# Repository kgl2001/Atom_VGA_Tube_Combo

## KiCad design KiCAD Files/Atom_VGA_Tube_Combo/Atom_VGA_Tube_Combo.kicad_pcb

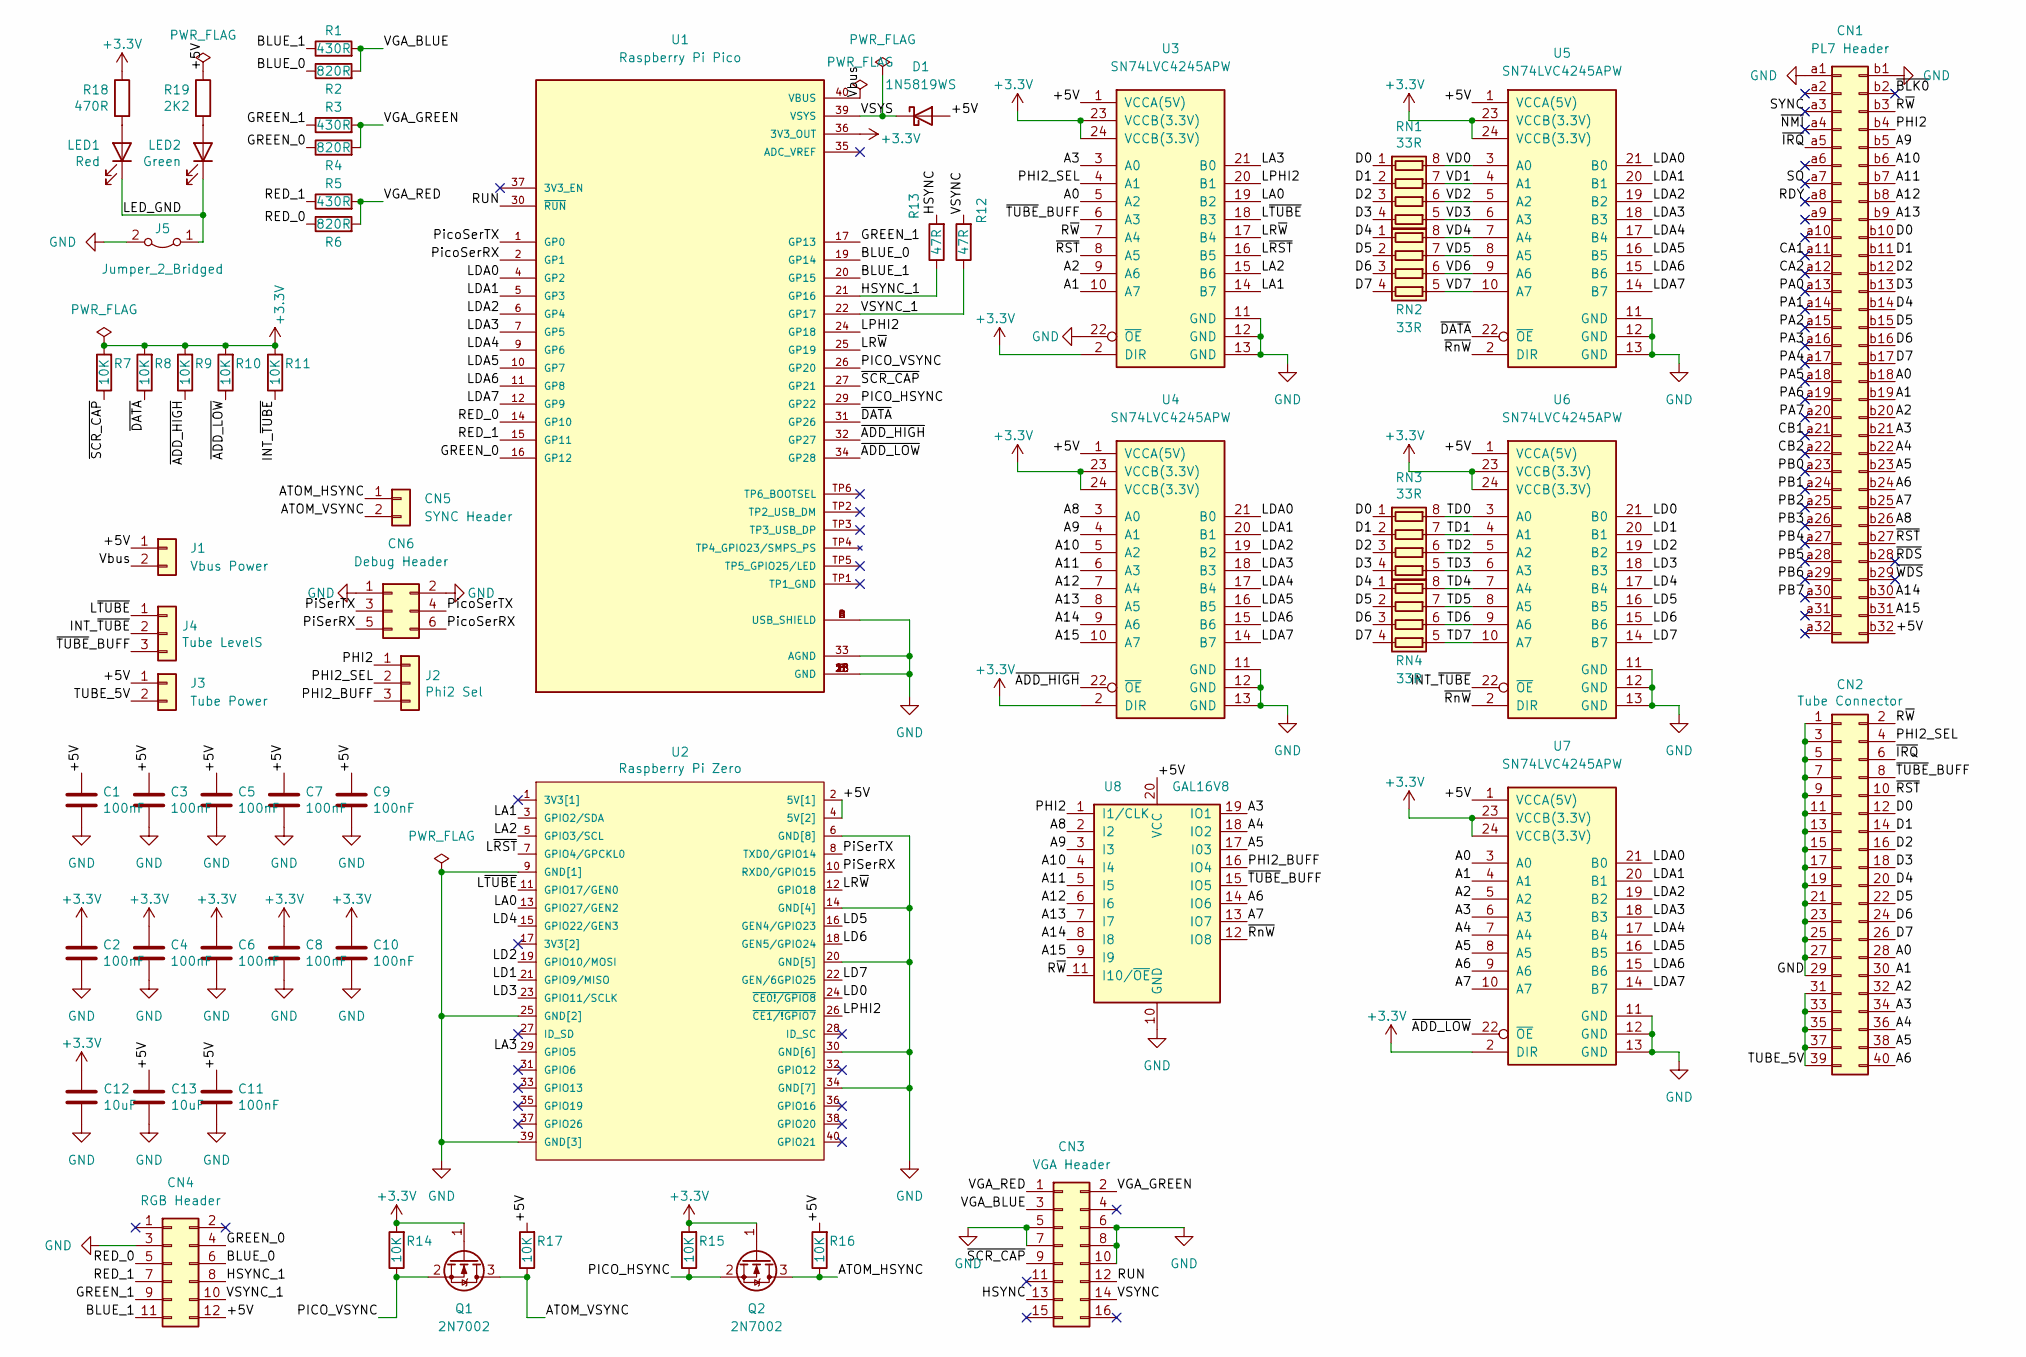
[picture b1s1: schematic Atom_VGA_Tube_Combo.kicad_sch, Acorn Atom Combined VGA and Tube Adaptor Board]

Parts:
C1, C2, C3, C4, C5, C6, C7, C8, C9, C10, C11: 100nF; C_0402_1005Metric; Tolerance 10%; JLC Part Number C1525
C12, C13: 10uF; C_0603_1608Metric; Tolerance 10%; JLC Part Number C19702
CN1: PL7 Header; DIN41612_Q_2x32_Male_Vertical_THT
CN2: Tube Connector; IDC-Header_2x20_P2.54mm_Horizontal
CN3: VGA Header; IDC-Header_2x08_P2.54mm_Vertical
CN4: RGB Header; IDC-Header_2x06_P2.54mm_Vertical
CN5: SYNC Header; PinHeader_2x01_P2.54mm_Horizontal
CN6: Debug Header; PinHeader_2x03_P2.54mm_Horizontal
D1: 1N5819WS; D_SOD-323; JLC Part Number C191023
J1: Vbus Power; PinHeader_1x02_P2.54mm_Vertical
J2: Phi2 Sel; PinHeader_1x03_P2.54mm_Vertical
J3: Tube Power; PinHeader_1x02_P2.54mm_Vertical
J4: Tube LevelS; PinHeader_1x03_P2.54mm_Vertical
J5: Jumper_2_Bridged; NetTie-2_THT_Pad1.0mmV2
LED1: Red; LED_0603_1608Metric; JLC Part Number C2286
LED2: Green; LED_0603_1608Metric; JLC Part Number C72043
Q1, Q2: 2N7002; SOT-23; JLC Part Number C8545
R1, R3, R5: 430R; R_0603_1608Metric; Tolerance 1%; JLC Part Number C23170
R2, R4, R6: 820R; R_0603_1608Metric; Tolerance 1%; JLC Part Number C23253
R7, R8, R9, R10, R11, R14, R15, R16, R17: 10K; R_0603_1608Metric; Tolerance 1%; JLC Part Number C25804
R12, R13: 47R; R_0603_1608Metric; Tolerance 1%; JLC Part Number C23182
R18: 470R; R_0603_1608Metric; Tolerance 1%; JLC Part Number C23179
R19: 2K2; R_0603_1608Metric; Tolerance 1%; JLC Part Number C4190
RN1, RN2, RN3, RN4: 33R; R_Array_Concave_4x0402; Tolerance 5%; JLC Part Number C25501
U1: Raspberry Pi Pico; RPI_PICO_DUAL_NoDebug; PARTREV 1.6
U2: Raspberry Pi Zero; RPI_ZERO_TH
U3, U4, U5, U6, U7: SN74LVC4245APW; TSSOP-24_4.4x7.8mm_P0.65mm; JLC Part Number C7859
U8: GAL16V8; DIP-20_W7.62mm

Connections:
+3.3V: C2.1, C4.1, C6.1, C8.1, C10.1, C12.1, Q1.1 (G), Q2.1 (G), R7.2, R8.2, R9.2, R10.2, R11.2, R14.2, R15.2, R18.1, U1.36 (3V3_OUT), U3.2 (DIR), U3.23 (VCCB(3.3V)), U3.24 (VCCB(3.3V)), U4.2 (DIR), U4.23 (VCCB(3.3V)), U4.24 (VCCB(3.3V)), U5.23 (VCCB(3.3V)), U5.24 (VCCB(3.3V)), U6.23 (VCCB(3.3V)), U6.24 (VCCB(3.3V)), U7.2 (DIR), U7.23 (VCCB(3.3V)), U7.24 (VCCB(3.3V))
/+5V: C1.1, C3.1, C5.1, C7.1, C9.1, C11.1, C13.1, CN1.b32, CN4.12, D1.2 (A), J1.1, J3.1, R16.2, R17.2, R19.1, U2.2 (5V[1]), U2.4 (5V[2]), U3.1 (VCCA(5V)), U4.1 (VCCA(5V)), U5.1 (VCCA(5V)), U6.1 (VCCA(5V)), U7.1 (VCCA(5V)), U8.20 (VCC)
/A0: CN1.b18, CN2.28, U3.5 (A2), U7.3 (A0)
/A1: CN1.b19, CN2.30, U3.10 (A7), U7.4 (A1)
/A2: CN1.b20, CN2.32, U3.9 (A6), U7.5 (A2)
/A3: CN1.b21, CN2.34, U3.3 (A0), U7.6 (A3), U8.19 (IO1)
/A4: CN1.b22, CN2.36, U7.7 (A4), U8.18 (IO2)
/A5: CN1.b23, CN2.38, U7.8 (A5), U8.17 (I03)
/A6: CN1.b24, CN2.40, U7.9 (A6), U8.14 (IO6)
/A7: CN1.b25, U7.10 (A7), U8.13 (IO7)
/A8: CN1.b26, U4.3 (A0), U8.2 (I2)
/A9: CN1.b5, U4.4 (A1), U8.3 (I3)
/A10: CN1.b6, U4.5 (A2), U8.4 (I4)
/A11: CN1.b7, U4.6 (A3), U8.5 (I5)
/A12: CN1.b8, U4.7 (A4), U8.6 (I6)
/A13: CN1.b9, U4.8 (A5), U8.7 (I7)
/A14: CN1.b30, U4.9 (A6), U8.8 (I8)
/A15: CN1.b31, U4.10 (A7), U8.9 (I9)
/ATOM_HSYNC: CN5.1, Q2.3 (D), R16.1
/ATOM_VSYNC: CN5.2, Q1.3 (D), R17.1
/BLUE_0: CN4.6, R2.1, U1.19 (GP14)
/BLUE_1: CN4.11, R1.1, U1.20 (GP15)
/CA1: CN1.a11
/CA2: CN1.a12
/CB1: CN1.a21
/CB2: CN1.a22
/D0: CN1.b10, CN2.12, RN1.1 (R1.1), RN3.1 (R1.1)
/D1: CN1.b11, CN2.14, RN1.2 (R2.1), RN3.2 (R2.1)
/D2: CN1.b12, CN2.16, RN1.3 (R3.1), RN3.3 (R3.1)
/D3: CN1.b13, CN2.18, RN1.4 (R4.1), RN3.4 (R4.1)
/D4: CN1.b14, CN2.20, RN2.1 (R1.1), RN4.1 (R1.1)
/D5: CN1.b15, CN2.22, RN2.2 (R2.1), RN4.2 (R2.1)
/D6: CN1.b16, CN2.24, RN2.3 (R3.1), RN4.3 (R3.1)
/D7: CN1.b17, CN2.26, RN2.4 (R4.1), RN4.4 (R4.1)
/GREEN_0: CN4.4, R4.1, U1.16 (GP12)
/GREEN_1: CN4.9, R3.1, U1.17 (GP13)
/HSYNC: CN3.13, R13.2
/HSYNC_1: CN4.8, R13.1, U1.21 (GP16)
/INT_~TUBE: J4.2, R11.1, U6.22 (~OE)
/LA0: U2.13 (GPIO27/GEN2), U3.19 (B2)
/LA1: U2.3 (GPIO2/SDA), U3.14 (B7)
/LA2: U2.5 (GPIO3/SCL), U3.15 (B6)
/LA3: U2.29 (GPIO5), U3.21 (B0)
/LD0: U2.24 (~CE0!/GPIO8), U6.21 (B0)
/LD1: U2.21 (GPIO9/MISO), U6.20 (B1)
/LD2: U2.19 (GPIO10/MOSI), U6.19 (B2)
/LD3: U2.23 (GPIO11/SCLK), U6.18 (B3)
/LD4: U2.15 (GPIO22/GEN3), U6.17 (B4)
/LD5: U2.16 (GEN4/GPIO23), U6.16 (B5)
/LD6: U2.18 (GEN5/GPIO24), U6.15 (B6)
/LD7: U2.22 (GEN/6GPIO25), U6.14 (B7)
/LDA0: U1.4 (GP2), U4.21 (B0), U5.21 (B0), U7.21 (B0)
/LDA1: U1.5 (GP3), U4.20 (B1), U5.20 (B1), U7.20 (B1)
/LDA2: U1.6 (GP4), U4.19 (B2), U5.19 (B2), U7.19 (B2)
/LDA3: U1.7 (GP5), U4.18 (B3), U5.18 (B3), U7.18 (B3)
/LDA4: U1.9 (GP6), U4.17 (B4), U5.17 (B4), U7.17 (B4)
/LDA5: U1.10 (GP7), U4.16 (B5), U5.16 (B5), U7.16 (B5)
/LDA6: U1.11 (GP8), U4.15 (B6), U5.15 (B6), U7.15 (B6)
/LDA7: U1.12 (GP9), U4.14 (B7), U5.14 (B7), U7.14 (B7)
/LED_GND: J5.1 (A), LED1.1 (K), LED2.1 (K)
/LPHI2: U1.24 (GP18), U2.26 (~CE1/!GPIO7), U3.20 (B1)
/LR~W: U1.25 (GP19), U2.12 (GPIO18), U3.17 (B4)
/L~RST: U2.7 (GPIO4/GPCKL0), U3.16 (B5)
/L~TUBE: J4.1, U2.11 (GPIO17/GEN0), U3.18 (B3)
/PA0: CN1.a13
/PA1: CN1.a14
/PA2: CN1.a15
/PA3: CN1.a16
/PA4: CN1.a17
/PA5: CN1.a18
/PA6: CN1.a19
/PA7: CN1.a20
/PB0: CN1.a23
/PB1: CN1.a24
/PB2: CN1.a25
/PB3: CN1.a26
/PB4: CN1.a27
/PB5: CN1.a28
/PB6: CN1.a29
/PB7: CN1.a30
/PHI2: CN1.b4, J2.1, U8.1 (I1/CLK)
/PHI2_BUFF: J2.3, U8.16 (IO4)
/PHI2_SEL: CN2.4, J2.2, U3.4 (A1)
/PICO_HSYNC: Q2.2 (S), R15.1, U1.29 (GP22)
/PICO_VSYNC: Q1.2 (S), R14.1, U1.26 (GP20)
/PiSerRX: CN6.5, U2.10 (RXD0/GPIO15)
/PiSerTX: CN6.3, U2.8 (TXD0/GPIO14)
/PicoSerRX: CN6.6, U1.2 (GP1)
/PicoSerTX: CN6.4, U1.1 (GP0)
/RDY: CN1.a8
/RED_0: CN4.5, R6.1, U1.14 (GP10)
/RED_1: CN4.7, R5.1, U1.15 (GP11)
/RUN: CN3.12, U1.30 (~RUN)
/R~W: CN1.b3, CN2.2, U3.7 (A4), U8.11 (I10/~OE)
/SO: CN1.a7
/SYNC: CN1.a3
/TD0: RN3.8 (R1.2), U6.3 (A0)
/TD1: RN3.7 (R2.2), U6.4 (A1)
/TD2: RN3.6 (R3.2), U6.5 (A2)
/TD3: RN3.5 (R4.2), U6.6 (A3)
/TD4: RN4.8 (R1.2), U6.7 (A4)
/TD5: RN4.7 (R2.2), U6.8 (A5)
/TD6: RN4.6 (R3.2), U6.9 (A6)
/TD7: RN4.5 (R4.2), U6.10 (A7)
/TUBE_5V: CN2.31, CN2.33, CN2.35, CN2.37, CN2.39, J3.2
/VD0: RN1.8 (R1.2), U5.3 (A0)
/VD1: RN1.7 (R2.2), U5.4 (A1)
/VD2: RN1.6 (R3.2), U5.5 (A2)
/VD3: RN1.5 (R4.2), U5.6 (A3)
/VD4: RN2.8 (R1.2), U5.7 (A4)
/VD5: RN2.7 (R2.2), U5.8 (A5)
/VD6: RN2.6 (R3.2), U5.9 (A6)
/VD7: RN2.5 (R4.2), U5.10 (A7)
/VGA_BLUE: CN3.3, R1.2, R2.2
/VGA_GREEN: CN3.2, R3.2, R4.2
/VGA_RED: CN3.1, R5.2, R6.2
/VSYNC: CN3.14, R12.2
/VSYNC_1: CN4.10, R12.1, U1.22 (GP17)
/VSYS: D1.1 (K), U1.39 (VSYS)
/Vbus: J1.2, U1.40 (VBUS)
/~ADD_HIGH: R9.1, U1.32 (GP27), U4.22 (~OE)
/~ADD_LOW: R10.1, U1.34 (GP28), U7.22 (~OE)
/~BLK0: CN1.b2
/~DATA: R8.1, U1.31 (GP26), U5.22 (~OE)
/~IRQ: CN1.a5, CN2.6
/~NMI: CN1.a4
/~RDS: CN1.b28
/~RST: CN1.b27, CN2.10, U3.8 (A5)
/~RnW: U5.2 (DIR), U6.2 (DIR), U8.12 (IO8)
/~SCR_CAP: CN3.9, R7.1, U1.27 (GP21)
/~TUBE_BUFF: CN2.8, J4.3, U3.6 (A3), U8.15 (IO5)
/~WDS: CN1.b29
GND: C1.2, C2.2, C3.2, C4.2, C5.2, C6.2, C7.2, C8.2, C9.2, C10.2, C11.2, C12.2, C13.2, CN1.a1, CN1.b1, CN2.1, CN2.3, CN2.5, CN2.7, CN2.9, CN2.11, CN2.13, CN2.15, CN2.17, CN2.19, CN2.21, CN2.23, CN2.25, CN2.27, CN2.29, CN3.5, CN3.6, CN3.7, CN3.8, CN3.10, CN4.3, CN6.1, CN6.2, J5.2 (B), U1.3 (GND), U1.8 (GND), U1.13 (GND), U1.18 (GND), U1.23 (GND), U1.28 (GND), U1.33 (AGND), U1.38 (GND), U1.A (USB_SHIELD), U1.B (USB_SHIELD), U1.C (USB_SHIELD), U1.D (USB_SHIELD), U2.6 (GND[8]), U2.9 (GND[1]), U2.14 (GND[4]), U2.20 (GND[5]), U2.25 (GND[2]), U2.30 (GND[6]), U2.34 (GND[7]), U2.39 (GND[3]), U3.11 (GND), U3.12 (GND), U3.13 (GND), U3.22 (~OE), U4.11 (GND), U4.12 (GND), U4.13 (GND), U5.11 (GND), U5.12 (GND), U5.13 (GND), U6.11 (GND), U6.12 (GND), U6.13 (GND), U7.11 (GND), U7.12 (GND), U7.13 (GND), U8.10 (GND)
unnamed: LED1.2 (A), R18.2
unnamed: LED2.2 (A), R19.2

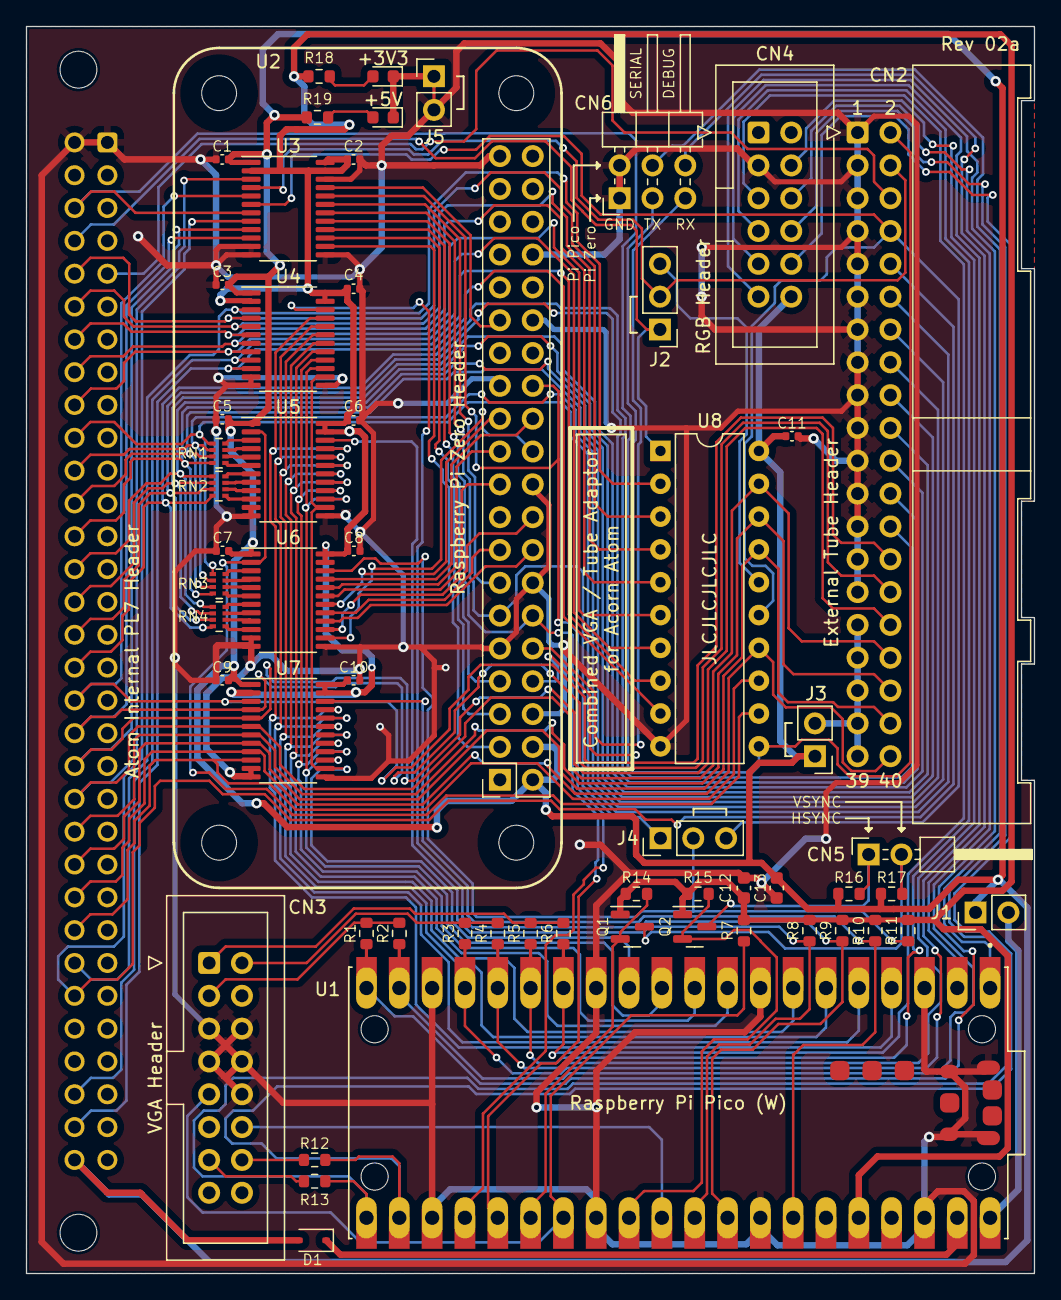
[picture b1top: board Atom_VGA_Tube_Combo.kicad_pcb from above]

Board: 4 copper layers, 78.0 x 96.5 mm, 60 parts (1 on the bottom side), 108 nets.

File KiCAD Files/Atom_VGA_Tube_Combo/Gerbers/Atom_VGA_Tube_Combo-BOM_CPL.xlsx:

Designator | LCSC Part # | Footprint | JLCValue | Mid X | Mid Y | Rotation | Layer | Val | Package
C1 | C1525 | 0402 | 100nF | 76.199999000000005 | -29.274000000000001 | 180 | top | 100nF | C_0402_1005Metric
C2 | C1525 | 0402 | 100nF | 86.359999000000002 | -29.274000000000001 | 0 | top | 100nF | C_0402_1005Metric
C3 | C1525 | 0402 | 100nF | 76.199999000000005 | -38.979999999999997 | 180 | top | 100nF | C_0402_1005Metric
C4 | C1525 | 0402 | 100nF | 86.359999000000002 | -39.284999999999997 | 0 | top | 100nF | C_0402_1005Metric
C5 | C1525 | 0402 | 100nF | 76.199999000000005 | -49.384999999999998 | 180 | top | 100nF | C_0402_1005Metric
C6 | C1525 | 0402 | 100nF | 86.359999000000002 | -49.473999999999997 | 0 | top | 100nF | C_0402_1005Metric
C7 | C1525 | 0402 | 100nF | 76.22 | -59.573999999999998 | 180 | top | 100nF | C_0402_1005Metric
C8 | C1525 | 0402 | 100nF | 86.38 | -59.573999999999998 | 0 | top | 100nF | C_0402_1005Metric
C9 | C1525 | 0402 | 100nF | 76.199999000000005 | -69.584999999999994 | 180 | top | 100nF | C_0402_1005Metric
C10 | C1525 | 0402 | 100nF | 86.359999000000002 | -69.584999999999994 | 0 | top | 100nF | C_0402_1005Metric
C11 | C1525 | 0402 | 100nF | 120.28649900000001 | -50.692999999999998 | 0 | top | 100nF | C_0402_1005Metric
C12 | C19702 | 0603 | 10uF | 116.5685 | -85.656599999999997 | 90 | top | 10uF | C_0603_1608Metric
C13 | C19702 | 0603 | 10uF | 119.10850000000001 | -85.656599999999997 | -90 | top | 10uF | C_0603_1608Metric
D1 | C191023 | SOD-323 | 1N5819WS | 83.185000000000002 | -112.923 | 180 | top | 1N5819WS | D_SOD-323
LED1 | C2286 | 0603 | Red | 88.645999000000003 | -22.849 | 180 | top | Red | LED_0603_1608Metric
LED2 | C72043 | 0603 | Green | 88.645999000000003 | -26.024000000000001 | 180 | top | Green | LED_0603_1608Metric
Q1 | C8545 | SOT-23 | 2N7002 | 107.9325 | -88.652000000000001 | 180 | top | 2N7002 | SOT-23
Q2 | C8545 | SOT-23 | 2N7002 | 112.7585 | -88.652000000000001 | 180 | top | 2N7002 | SOT-23
R1 | C23170 | 0603 | 430R | 87.358500000000006 | -89.174000000000007 | 90 | top | 430R | R_0603_1608Metric
R2 | C23253 | 0603 | 820R | 89.898499999999999 | -89.174000000000007 | 90 | top | 820R | R_0603_1608Metric
R3 | C23170 | 0603 | 430R | 94.978499999999997 | -89.174000000000007 | 90 | top | 430R | R_0603_1608Metric
R4 | C23253 | 0603 | 820R | 97.518500000000003 | -89.174000000000007 | 90 | top | 820R | R_0603_1608Metric
R5 | C23170 | 0603 | 430R | 100.0585 | -89.174000000000007 | 90 | top | 430R | R_0603_1608Metric
R6 | C23253 | 0603 | 820R | 102.5985 | -89.174000000000007 | 90 | top | 820R | R_0603_1608Metric
R7 | C25804 | 0603 | 10K | 116.5685 | -88.958600000000004 | 90 | top | 10K | R_0603_1608Metric
R8 | C25804 | 0603 | 10K | 121.6485 | -88.958600000000004 | 90 | top | 10K | R_0603_1608Metric
R9 | C25804 | 0603 | 10K | 124.1885 | -88.958600000000004 | 90 | top | 10K | R_0603_1608Metric
R10 | C25804 | 0603 | 10K | 126.7285 | -88.958600000000004 | 90 | top | 10K | R_0603_1608Metric
R11 | C25804 | 0603 | 10K | 129.26849999999999 | -88.956599999999995 | 90 | top | 10K | R_0603_1608Metric
R12 | C23182 | 0603 | 47R | 83.348500000000001 | -106.7 | 180 | top | 47R | R_0603_1608Metric
R13 | C23182 | 0603 | 47R | 83.348500000000001 | -108.351 | 180 | top | 47R | R_0603_1608Metric
R14 | C25804 | 0603 | 10K | 108.2495 | -86.111999999999995 | 180 | top | 10K | R_0603_1608Metric
R15 | C25804 | 0603 | 10K | 113.0125 | -86.111999999999995 | 180 | top | 10K | R_0603_1608Metric
R16 | C25804 | 0603 | 10K | 124.6965 | -86.111999999999995 | 180 | top | 10K | R_0603_1608Metric
R17 | C25804 | 0603 | 10K | 127.99850000000001 | -86.111999999999995 | 180 | top | 10K | R_0603_1608Metric
R18 | C23179 | 0603 | 470R | 83.692999 | -22.849 | 0 | top | 470R | R_0603_1608Metric
R19 | C4190 | 0603 | 2K2 | 83.565999000000005 | -26.024000000000001 | 0 | top | 2K2 | R_0603_1608Metric
RN1 | C25501 | 0402_x4 | 33R | 75.945999 | -52.014000000000003 | -90 | top | 33R | R_Array_Concave_4x0402
RN2 | C25501 | 0402_x4 | 33R | 75.945999 | -54.554000000000002 | -90 | top | 33R | R_Array_Concave_4x0402
RN3 | C25501 | 0402_x4 | 33R | 75.965999999999994 | -62.113999999999997 | -90 | top | 33R | R_Array_Concave_4x0402
RN4 | C25501 | 0402_x4 | 33R | 75.965999999999994 | -64.653999999999996 | -90 | top | 33R | R_Array_Concave_4x0402
U3 | C7859 | TSSOP-24 | SN74LVC4245APW | 81.3 | -33.084000000000003 | -90 | top | SN74LVC4245APW | TSSOP-24_4.4x7.8mm_P0.65mm
U4 | C7859 | TSSOP-24 | SN74LVC4245APW | 81.3 | -43.183999999999997 | -90 | top | SN74LVC4245APW | TSSOP-24_4.4x7.8mm_P0.65mm
U5 | C7859 | TSSOP-24 | SN74LVC4245APW | 81.3 | -53.283999999999999 | -90 | top | SN74LVC4245APW | TSSOP-24_4.4x7.8mm_P0.65mm
U6 | C7859 | TSSOP-24 | SN74LVC4245APW | 81.3 | -63.384 | -90 | top | SN74LVC4245APW | TSSOP-24_4.4x7.8mm_P0.65mm
U7 | C7859 | TSSOP-24 | SN74LVC4245APW | 81.3 | -73.483999999999995 | -90 | top | SN74LVC4245APW | TSSOP-24_4.4x7.8mm_P0.65mm

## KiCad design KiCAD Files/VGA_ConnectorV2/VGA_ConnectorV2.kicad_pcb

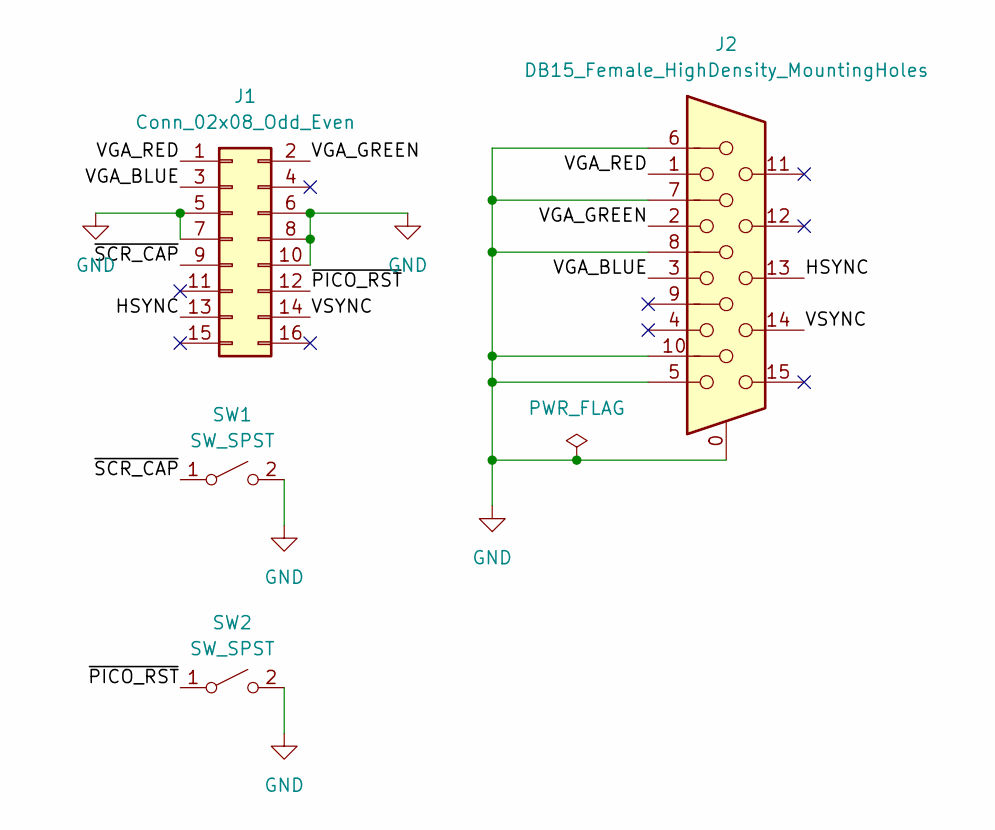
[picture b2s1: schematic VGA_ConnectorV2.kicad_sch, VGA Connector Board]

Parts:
J1: Conn_02x08_Odd_Even; IDC-Header_2x08_P2.54mm_Vertical
J2: DB15_Female_HighDensity_MountingHoles; DSUB-15-HD_Female_Horizontal_P2.29x1.98mm_EdgePinOffset3.03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
SW1, SW2: SW_SPST; SW_PUSH_6mm

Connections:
/HSYNC: J1.13, J2.13
/VGA_BLUE: J1.3, J2.3
/VGA_GREEN: J1.2, J2.2
/VGA_RED: J1.1, J2.1
/VSYNC: J1.14, J2.14
/~PICO_RST: J1.12, SW2.1 (A)
/~SCR_CAP: J1.9, SW1.1 (A)
GND: J1.5, J1.6, J1.7, J1.8, J1.10, J2.0, J2.5, J2.6, J2.7, J2.8, J2.10, SW1.2 (B), SW2.2 (B)

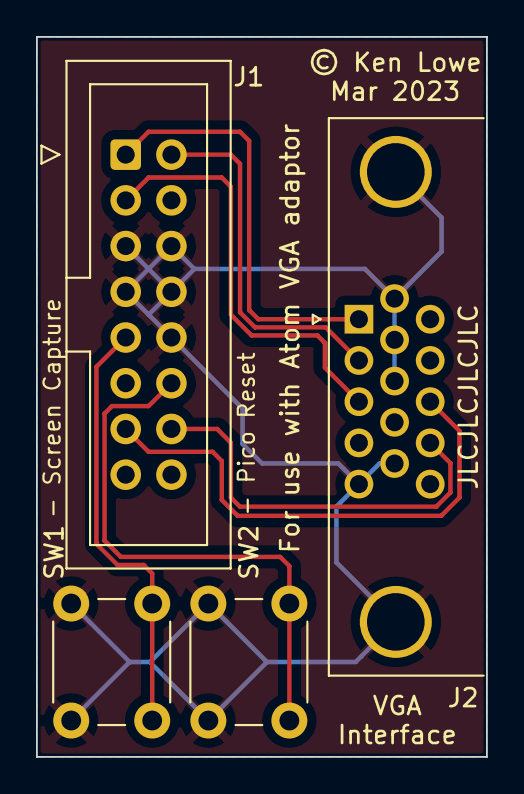
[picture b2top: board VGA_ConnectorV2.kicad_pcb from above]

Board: 2 copper layers, 25.0 x 40.0 mm, 4 parts (0 on the bottom side), 8 nets.

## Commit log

2023-10-03 VGA Connector - Initial Commit
2023-10-03 IC4 Databus Bypass - Initial Commit
2023-10-03 Atom VGA / RGB & Tube Combo Board - Initial Commit
2023-10-03 U8 PLD Logic - Initial Commit
2023-10-03 AtomVGA Pico Firmware - Initial Commit

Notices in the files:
KiCAD Files/Atom_VGA_Tube_Combo/Atom_VGA_Tube_Combo.kicad_pcb:
© Ken Lowe
